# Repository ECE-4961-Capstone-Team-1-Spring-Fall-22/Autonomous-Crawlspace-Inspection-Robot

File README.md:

# Autonomous-Crawlspace-Inspection-Robot
This GitHub contains all relevant files used during development. For a comprehensive guide to the repository set up see the bottom of the document.
## Executive Summary
Crawl spaces grant convenient access to the plumbing, duct work, and electrical wiring of a house, but they often present unique dangers to maintenance professionals and residents alike. Exposure to harsh breathing conditions, hanging obstacles, uncomfortable working positions, and even animals can cause non-ideal conditions. This capstone project will focus on the design and assembly of a robot prototype that can perform these inspections autonomously. The end product will be an autonomous, mobile robot that can be left unattended in a crawlspace by an inspector. It will navigate through the space, create a map and model of the space, compile an image of the entire crawlspace ceiling, and collect sensor data. This sensor data will include humidity, temperature, and wood moisture content.

## Current Robot Capabilities
The first iteration of the project focused on setting up the hardware systems. Sensors, microcontrollers, motors, and power circuits were designed and implemented as part of a larger multi-group project. The following details the current capabilities of the robot.

* Low-level autonomy which allows the robot to navigate through an enclosed area
* Creating a map of the area using the SLAM algorithm
* Take pictures throughout an area and stitch simple areas into a singular, larger image
* Collect humidity, temperature, and moisture content data and overlay information on images
* Supply power for consistent operation across all components
* Robot movement through serial commands and return encoder data to the main microcontroller
* Manual control through text-based commands while also streaming live video to the operator

For more detail on current designs, see files in sub-system directories

## Salient Outcomes
Although this project includes lofty long-term goals, many exceptional systems were able to be incorporated in the first iteration of the project.
* The mapping was found to be accurate to 93% or more in each test that was run. While this is useful information for an inspector to have, it will also provide an invaluable framework for future updates to the autonomy
* Power was successfully applied to all parts of the system with no over-currents or under-voltages experienced by the system. All back EMF from the motors was successfully filtered out as well.
* Environmental sensing was found to be exceptionally accurate. Temperature and Humidity were both found to be 96% accurate or greater while moisture content was successfully measured to within 2.5% moisture.

## Pictures and Videos
The final system demo in the crawlspace can be found [here](https://www.youtube.com/watch?v=mYopD1X_bd8&t=9s)

A picture of the final system can also be found below 

## Who Are We? Mr. Jesse Robert's ECE 4961 Capstone Team 1

* James (Jim) Camp - Senior Electrical Engineering Major, Mechatronics Concentration - Environmental Sensor Subsystem Developer - Delegator 
* John-Caleb (JC) Williams - Senior Electrical Engineering Major, Electromagnetics Concentration - Navigation Subsystem Developer - Treasurer
* John Harris - Senior Electrical Engineering Major, Controls Concentration - Power Subsystem Developer - Secretary
* Joseph Thomas - Senior Electrical Engineering Major, Power Concentration - Movement Subsystem Developer - Social 

* Mr. Jesse Roberts - Professor and Faculty Advisor

* Project Stakeholders - This project was developed for anyone who needs to inspect their crawlspace. This includes homeowners, building inspectors, and renovators. The system is also a great solution for anyone experiencing issues with mold or unsafe crawlspace conditions.

# Repo Guide
This repository contains the entirety of the Autonomous Crawlspace Inspection Robot’s REV1 design files. The folder breakdown is as follows
* Design Files – Contains files that represent the final design state of the project. This is made up of an overall system schematic and the bill of materials (BOM).
* Documentation – Contains all written submissions created throughout both semesters of the course. Also included are the presentations used at the end of the project.
* Environmental Sensing – This subsystem is responsible for the data collection which occurs throughout the crawlspace. Additionally, image stitching is also included within this folder.
* Movement – This subsystem is responsible for controlling the physical motion and positioning of the robot. 
* Navigation – This system handles the mapping and autonomy. Interfacing with the Raspberry Pi, LIDAR, distance sensors, and remote access are also included in this subsystem.
* Pictures and Videos – A repository for all the pictures and videos taken throughout the experimentation and testing.
* Power - This subsystem is responsible for providing continuous power to all the components. Circuit protection and power filtering are also integrated into this subsystem.

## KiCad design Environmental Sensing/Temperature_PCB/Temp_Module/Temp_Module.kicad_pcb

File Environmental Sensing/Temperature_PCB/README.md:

## Temperature Module PCB
Enclosed are the Kicad files for the temperature sensor PCB. This board is designed to be apart of and sensor board stack which uses the standoff parts found in the BOM.

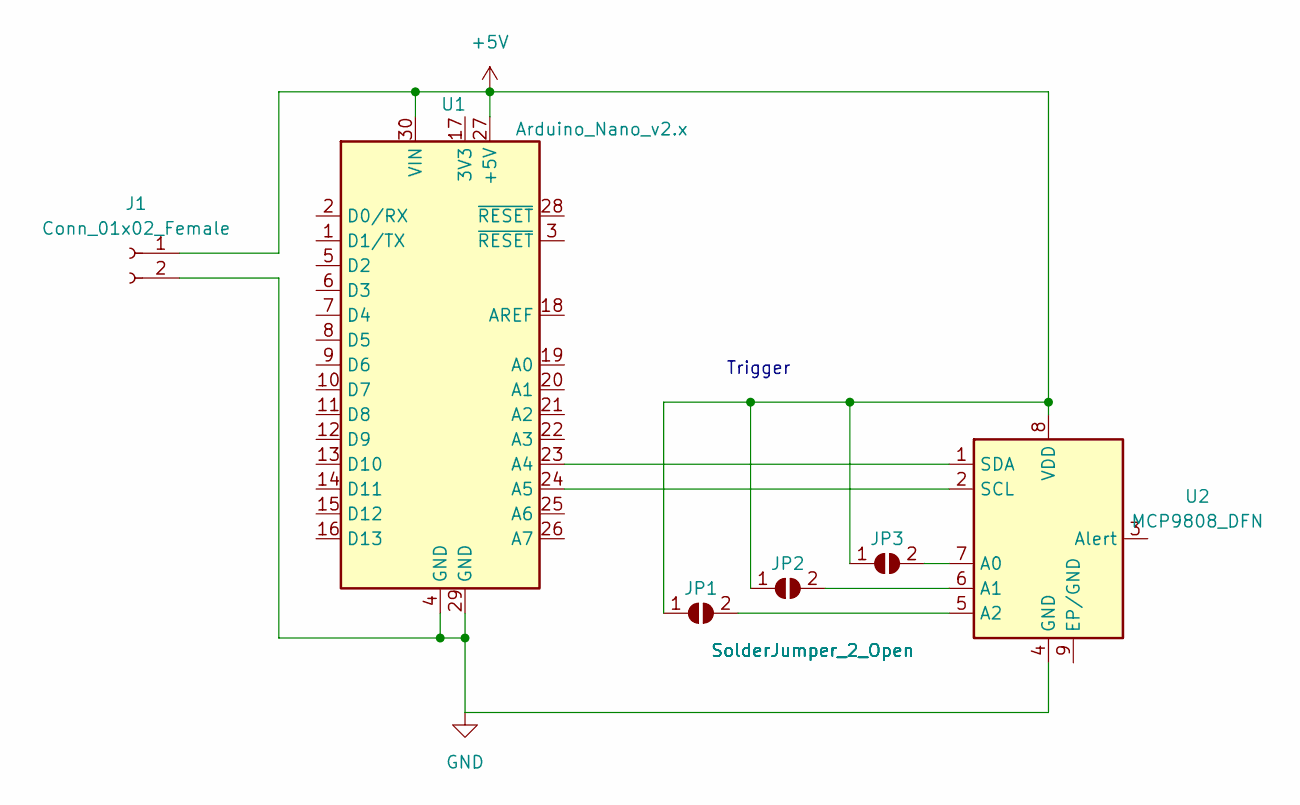
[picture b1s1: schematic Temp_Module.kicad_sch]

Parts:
J1: Conn_01x02_Female; PinHeader_1x02_P2.54mm_Vertical
JP1, JP2, JP3: SolderJumper_2_Open; SolderJumper-2_P1.3mm_Bridged2Bar_Pad1.0x1.5mm
U1: Arduino_Nano_v2.x; Arduino_Nano_WithMountingHoles
U2: MCP9808_DFN; DFN-8-1EP_3x2mm_P0.5mm_EP1.7x1.4mm

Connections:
+5V: J1.1, JP1.1 (A), JP2.1 (A), JP3.1 (A), U1.27 (+5V), U1.30 (VIN), U2.8 (VDD)
GND: J1.2, U1.4 (GND), U1.29 (GND), U2.4 (GND)
unnamed: JP1.2 (B), U2.5 (A2)
unnamed: JP2.2 (B), U2.6 (A1)
unnamed: JP3.2 (B), U2.7 (A0)
unnamed: U1.23 (A4), U2.1 (SDA)
unnamed: U1.24 (A5), U2.2 (SCL)

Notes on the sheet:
Trigger

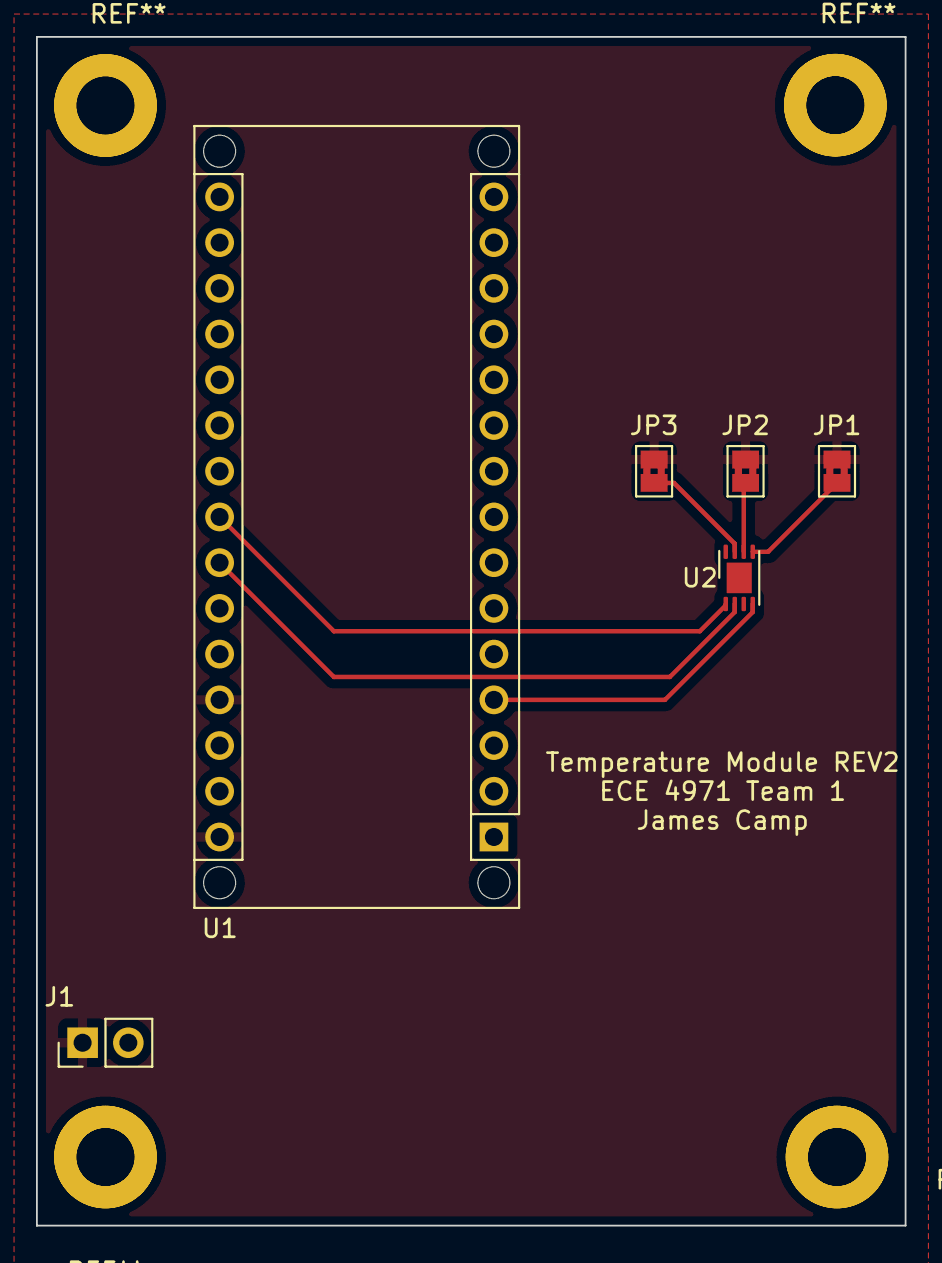
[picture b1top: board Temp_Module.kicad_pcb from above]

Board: 2 copper layers, 48.3 x 66.0 mm, 6 parts (0 on the bottom side), 7 nets.

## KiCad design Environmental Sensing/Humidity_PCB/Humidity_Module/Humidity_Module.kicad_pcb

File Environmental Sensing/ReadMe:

#Enviromental Sensing System

#Specs, Design, and Analysis:
This system was required to analyze data when triggered by the overall Raspberry Pi
It was also required to be modular and include a temperature sensor, humidity sensor, and wood moistrue probe

To match these rquirements, a system was developed where each sensor had its own MCU and returns data to the Raspberry Pi using SPI protocal
Each MCU will runs its respective sensor to collect a predetermined number of samples and then return the average to the Pi
A tag is inlcuded with the number so the Pi can differentiate between what was being sensed
This also allows future sensors to be easily added.

A wood moistrue probe was also included
This includes a two phase linear actuator design to raise the probe from 15 inches to 48 inches
Once in the wood, a resistance measurment is taken to detect MC%

Circuit Analysis as well as calculations were performed to verify each sysem

This README file constitutes a summary, for detailed design information and analysis of each component see signoff files in this repository

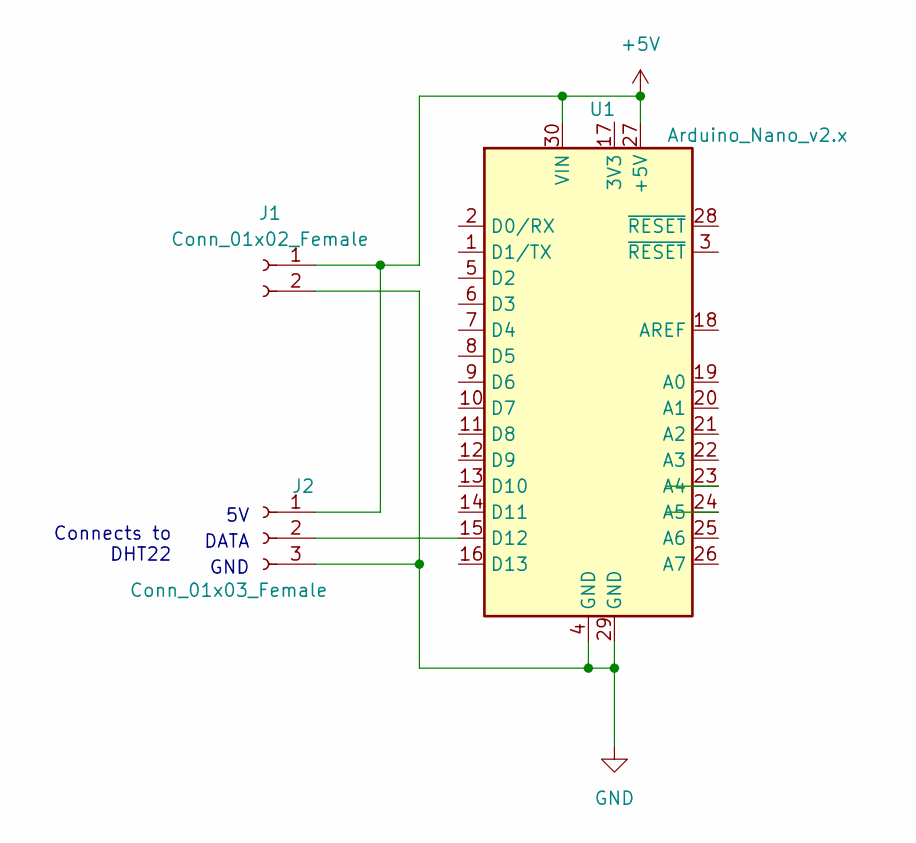
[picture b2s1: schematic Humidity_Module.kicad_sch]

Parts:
J1: Conn_01x02_Female; PinHeader_1x02_P2.54mm_Vertical
J2: Conn_01x03_Female; PinHeader_1x03_P2.54mm_Horizontal
U1: Arduino_Nano_v2.x; Arduino_Nano

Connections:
+5V: J1.1, J2.1, U1.27 (+5V), U1.30 (VIN)
GND: J1.2, J2.3, U1.4 (GND), U1.29 (GND)
unnamed: J2.2, U1.15 (D12)

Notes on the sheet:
Connects to DHT22
GND
DATA

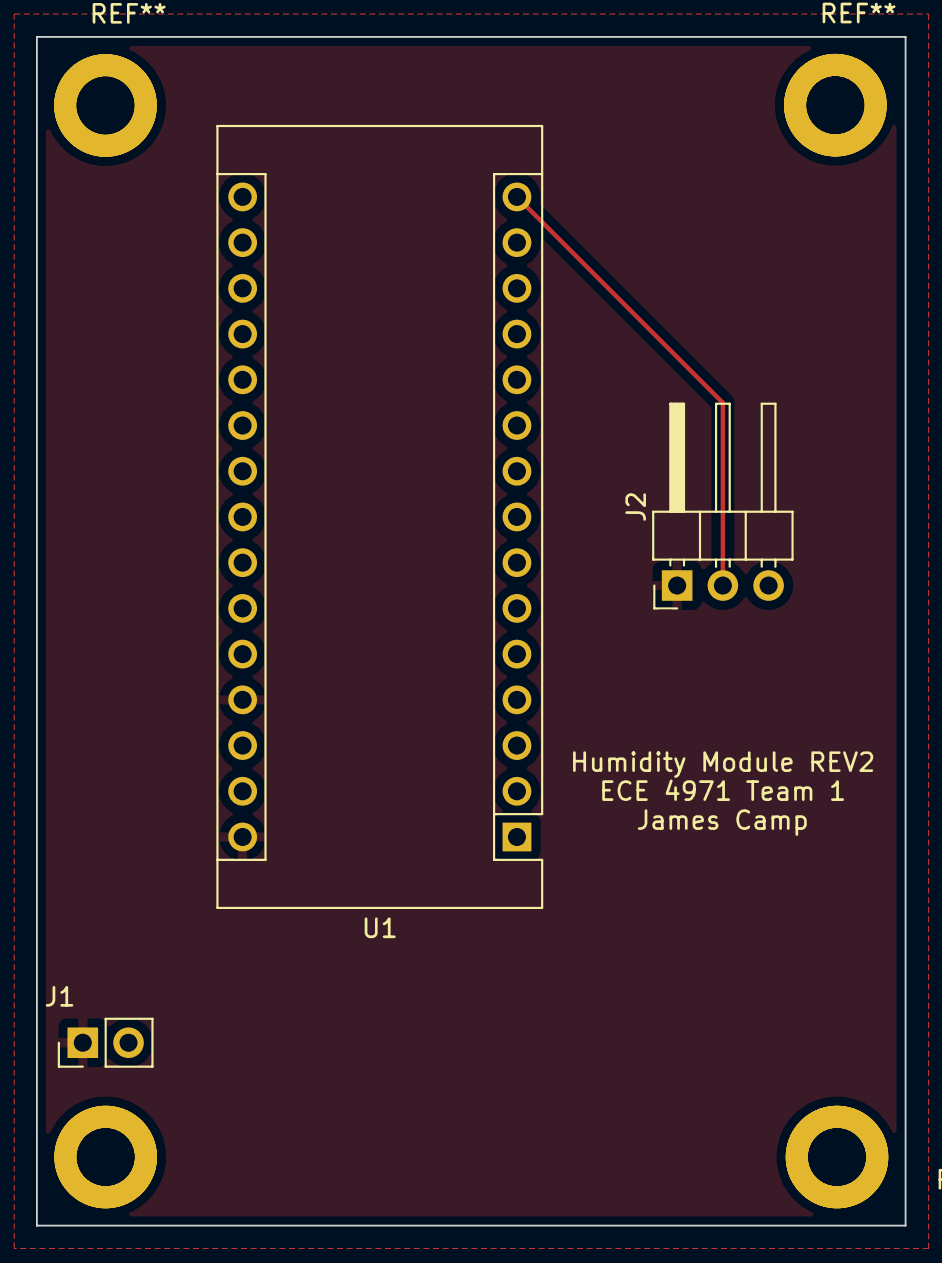
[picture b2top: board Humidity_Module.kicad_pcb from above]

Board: 2 copper layers, 48.3 x 66.0 mm, 3 parts (0 on the bottom side), 3 nets.

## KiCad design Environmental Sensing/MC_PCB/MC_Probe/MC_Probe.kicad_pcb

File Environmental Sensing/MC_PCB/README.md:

## Moisture Content Probe Module PCB
Enclosed are the Kicad files for the moisture content sensor PCB. This board is designed to be apart of and sensor board stack which uses the standoff parts found in the BOM. 
Terminal blocks are included to allow connection to the external circuit parts such as the motor driver and probe. Connections for these parts are found in the schematic pdf.

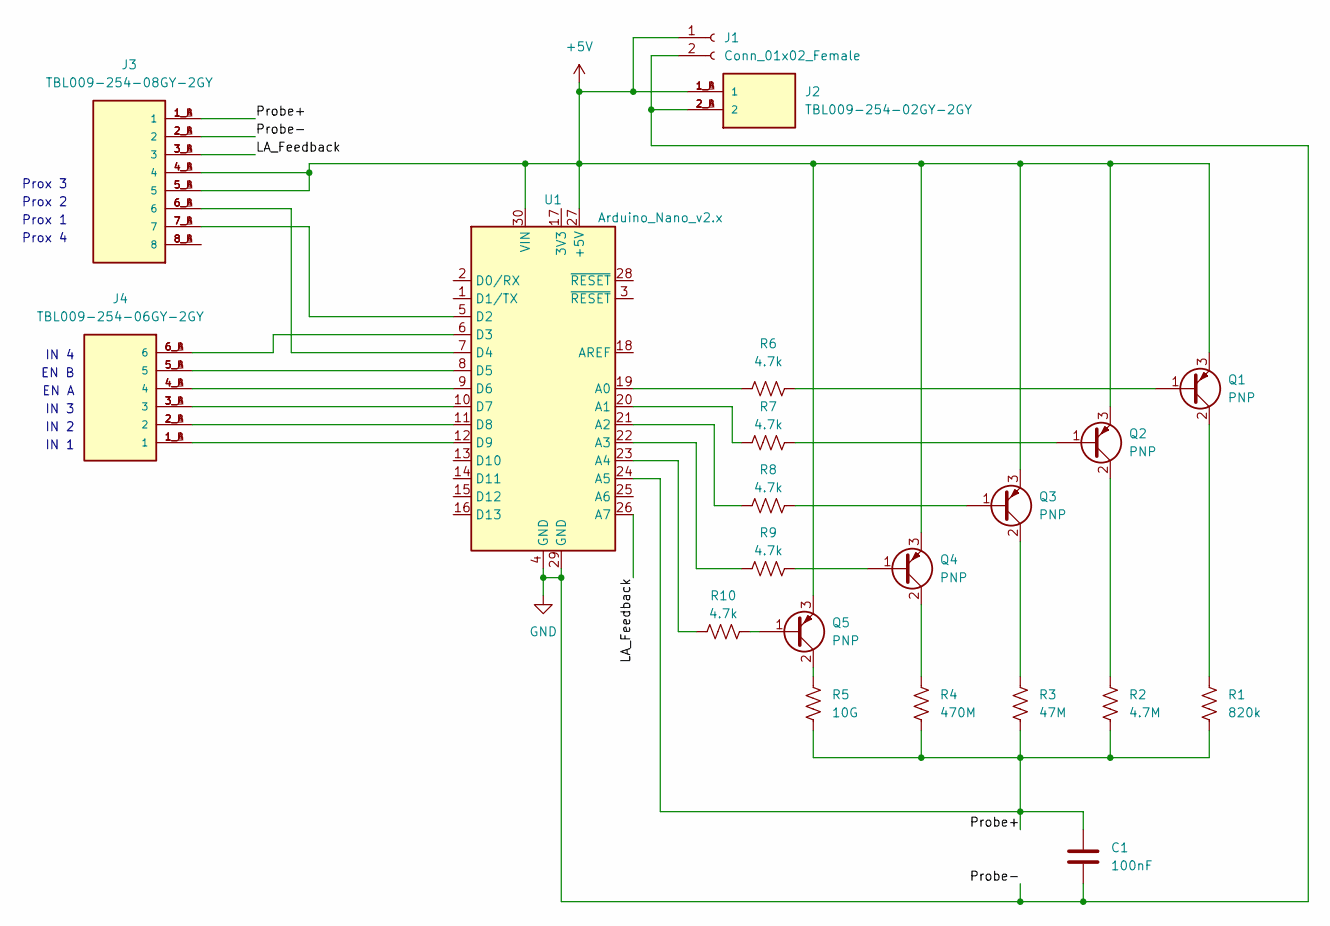
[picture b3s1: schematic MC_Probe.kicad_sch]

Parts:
C1: 100nF; C_1206_3216Metric
J1: Conn_01x02_Female; PinHeader_1x02_P2.54mm_Vertical
J2: TBL009-254-02GY-2GY; CUI_TBL009-254-02GY-2GY
J3: TBL009-254-08GY-2GY; CUI_TBL009-254-08GY-2GY
J4: TBL009-254-06GY-2GY; CUI_TBL009-254-06GY-2GY
Q1, Q2, Q3, Q4, Q5: PNP; TO-92
R1: 820k; R_1206_3216Metric
R2: 4.7M; R_1206_3216Metric
R3: 47M; R_1206_3216Metric
R4: 470M; R_1206_3216Metric
R5: 10G; R_1206_3216Metric
R6, R7, R8, R9, R10: 4.7k; R_1206_3216Metric
U1: Arduino_Nano_v2.x; Arduino_Nano_WithMountingHoles

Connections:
+5V: J1.1, J2.1_A (1), J2.1_B (1), J3.4_A (4), J3.4_B (4), J3.5_A (5), J3.5_B (5), Q1.3 (E), Q2.3 (E), Q3.3 (E), Q4.3 (E), Q5.3 (E), U1.27 (+5V), U1.30 (VIN)
/LA_Feedback: J3.3_A (3), J3.3_B (3), U1.26 (A7)
/Probe+: C1.1, J3.1_A (1), J3.1_B (1), R1.2, R2.2, R3.2, R4.2, R5.2, U1.24 (A5)
GND: C1.2, J1.2, J2.2_A (2), J2.2_B (2), J3.2_A (2), J3.2_B (2), U1.4 (GND), U1.29 (GND)
unnamed: J3.8_A (8), J3.8_B (8)
unnamed: J4.1_A (1), J4.1_B (1), U1.12 (D9)
unnamed: J4.2_A (2), J4.2_B (2), U1.11 (D8)
unnamed: J4.3_A (3), J4.3_B (3), U1.10 (D7)
unnamed: J4.4_A (4), J4.4_B (4), U1.9 (D6)
unnamed: J4.5_A (5), J4.5_B (5), U1.8 (D5)
unnamed: J4.6_A (6), J4.6_B (6), U1.6 (D3)
unnamed: Q1.1 (B), R6.2
unnamed: Q1.2 (C), R1.1
unnamed: Q2.1 (B), R7.2
unnamed: Q2.2 (C), R2.1
unnamed: Q3.1 (B), R8.2
unnamed: Q3.2 (C), R3.1
unnamed: Q4.2 (C), R4.1
unnamed: Q5.1 (B), R10.2
unnamed: Q5.2 (C), R5.1
unnamed: Q4.1 (B), R9.2
unnamed: J3.7_A (7), J3.7_B (7), U1.5 (D2)
unnamed: J3.6_A (6), J3.6_B (6), U1.7 (D4)
unnamed: R6.1, U1.19 (A0)
unnamed: R7.1, U1.20 (A1)
unnamed: R8.1, U1.21 (A2)
unnamed: R9.1, U1.22 (A3)
unnamed: R10.1, U1.23 (A4)

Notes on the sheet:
Prox 2
EN A
IN 1
EN B
IN 2
Prox 4
IN 4
Prox 3
IN 3
Prox 1

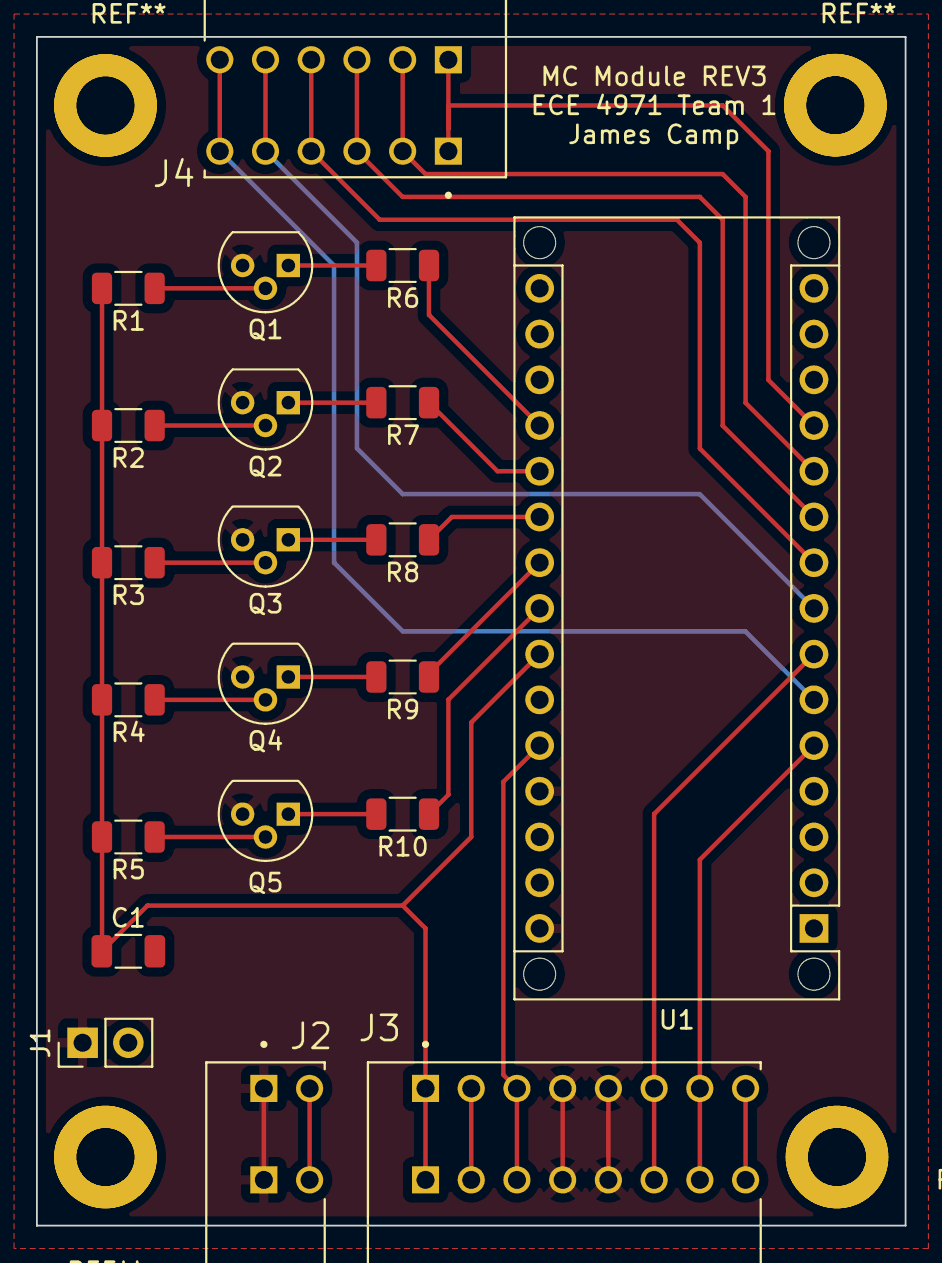
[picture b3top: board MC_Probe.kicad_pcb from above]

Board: 2 copper layers, 48.3 x 66.0 mm, 21 parts (0 on the bottom side), 28 nets.

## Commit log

2022-05-06 Create Mech Move Software Plans
2022-05-06 Add files via upload
    This is the first outline of the power schematic
2022-05-06 Add files via upload
    Picture of Buck Converter Research
2022-05-06 Add files via upload
    battery adapter schematic
2022-05-06 Create Software Plans
2022-11-04 Create Experimental Data
2022-11-05 Update Experimental Data.md
    This is a big commitment
2022-11-08 Update Experimental Data.md
    big commitment
2022-11-16 Create Camera2_Test
2022-11-16 Rename ImageStitchingTest/README to ExperimentalPictures/README
2022-11-16 Create ExperimentalPictures
2022-11-30 Added Good Signoffs
2022-11-30 Create Humidity_PCB
2022-11-30 Rename Experimental Data.md to Documentation/Experimental Data.md
2022-11-30 Rename Software_Writeup.md to Documentation/Software_Writeup.md
